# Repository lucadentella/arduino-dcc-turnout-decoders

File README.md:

# DCC turnout decoders and boards for Arduino

## :mega: Introduction / *Introduzione*
This repository contains all the resources for my tutorials about how to build DCC turnout (accessory) decoders with Arduino.

*Questo repository contiene tutte le risorse per i miei tutorial sulla costruzione di decoder scambi (accessori) DCC con Arduino.*

## :link: Links

 - [Youtube, Tutorial #1](https://youtu.be/FdMyOsOrDqg)
 - [Youtube, Tutorial #2](https://youtu.be/kijxEFWHnvc)
 - [Youtube, Tutorial #3](https://youtu.be/DjH3sCA5Gzo)
 - [Youtube, ServoShield](https://youtu.be/rDGcTmMk3Rc)
 - [Youtube, SoundShield](https://youtu.be/pyPB2XuQQIc)
 - [Youtube, Playlist](https://youtube.com/playlist?list=PL45uNmSXju7mn3bMtVVPlFQmpD3mUI5mi)
 
 - [Officina del Modellismo](https://www.officinamodellismo.com/), to buy our products / *per acquistare i nostri prodotti*
 - [Shared projects on PCBWay](https://www.pcbway.com/project/member/?bmbno=20B30179-F6D7-49), to order PCBs / *per ordinare i circuiti stampati*

## :barber: Boards / *Schede*
The [Eagle](https://github.com/lucadentella/arduino-dcc-turnout-decoders/tree/main/Eagle) subfolder contains [Eagle projects](https://www.autodesk.com/products/eagle/overview) to build the following boards (click on the board name to open the documentation with partlist, images...):

 - **[MosfetBoard](https://github.com/lucadentella/arduino-dcc-turnout-decoders/blob/main/Documentation/MosfetBoard.md)**, to control a solenoid motor using logic-level MOSFETs
 - **[PointMotorBoard](https://github.com/lucadentella/arduino-dcc-turnout-decoders/blob/main/Documentation/PointMotorBoard.md)**, to control two DC motors using an H-Bridge IC
 - **[CDU (Capacitor Discharge Unit)](https://github.com/lucadentella/arduino-dcc-turnout-decoders/blob/main/Documentation/CDU.md)**, to provide more current to actuators 
 - **[ServoShield](https://github.com/lucadentella/arduino-dcc-turnout-decoders/blob/main/Documentation/ServoShield.md)**, to create a Servo accessory decoder
 - **[SoundShield](https://github.com/lucadentella/arduino-dcc-turnout-decoders/blob/main/Documentation/SoundShield.md)**, to create a Sound accessory decoder

*La sottocartella [Eagle](https://github.com/lucadentella/arduino-dcc-turnout-decoders/tree/main/Eagle) contiene contiene dei [progetti Eagle](https://www.autodesk.com/products/eagle/overview) per realizzare le seguenti schede (clicca sul nome della scheda per aprire la relativa documentazione con elenco componenti, immagini...):*

 - **[MosfetBoard](https://github.com/lucadentella/arduino-dcc-turnout-decoders/blob/main/Documentation/MosfetBoard.md)**, per controllare un attuatore a solenoide usando logic-level MOSFETs
 - **[PointMotorBoard](https://github.com/lucadentella/arduino-dcc-turnout-decoders/blob/main/Documentation/PointMotorBoard.md)**, per controllare due motori in corrente continua usando un integrato H-Bridge
 - **[CDU (Capacitor Discharge Unit)](https://github.com/lucadentella/arduino-dcc-turnout-decoders/blob/main/Documentation/CDU.md)**, per fornire più corrente agli attuatori
 - **[ServoShield](https://github.com/lucadentella/arduino-dcc-turnout-decoders/blob/main/Documentation/ServoShield.md)**, per realizzare un decoder accessori per servocomandi
 - **[SoundShield](https://github.com/lucadentella/arduino-dcc-turnout-decoders/blob/main/Documentation/SoundShield.md)**, per realizzare un decoder accessori sonoro
 
## :clipboard: Sketches
The [Arduino](https://github.com/lucadentella/arduino-dcc-turnout-decoders/tree/main/Arduino) subfolder contains the sketches for implementing the decoders shown in the video tutorials.

*La sottocartella [Arduino](https://github.com/lucadentella/arduino-dcc-turnout-decoders/tree/main/Arduino) contiene i programmi (sketch) per realizzare i decoder mostrati nei video tutorials.*
 
## :factory: Documentation
The [Documentation](https://github.com/lucadentella/arduino-dcc-turnout-decoders/tree/main/Documentation) subfolder contains partlist, schematics

*La sottocartella [Documentation](https://github.com/lucadentella/arduino-dcc-turnout-decoders/tree/main/Documentation) contiene la lista dei componenti e gli schemi elettrici*

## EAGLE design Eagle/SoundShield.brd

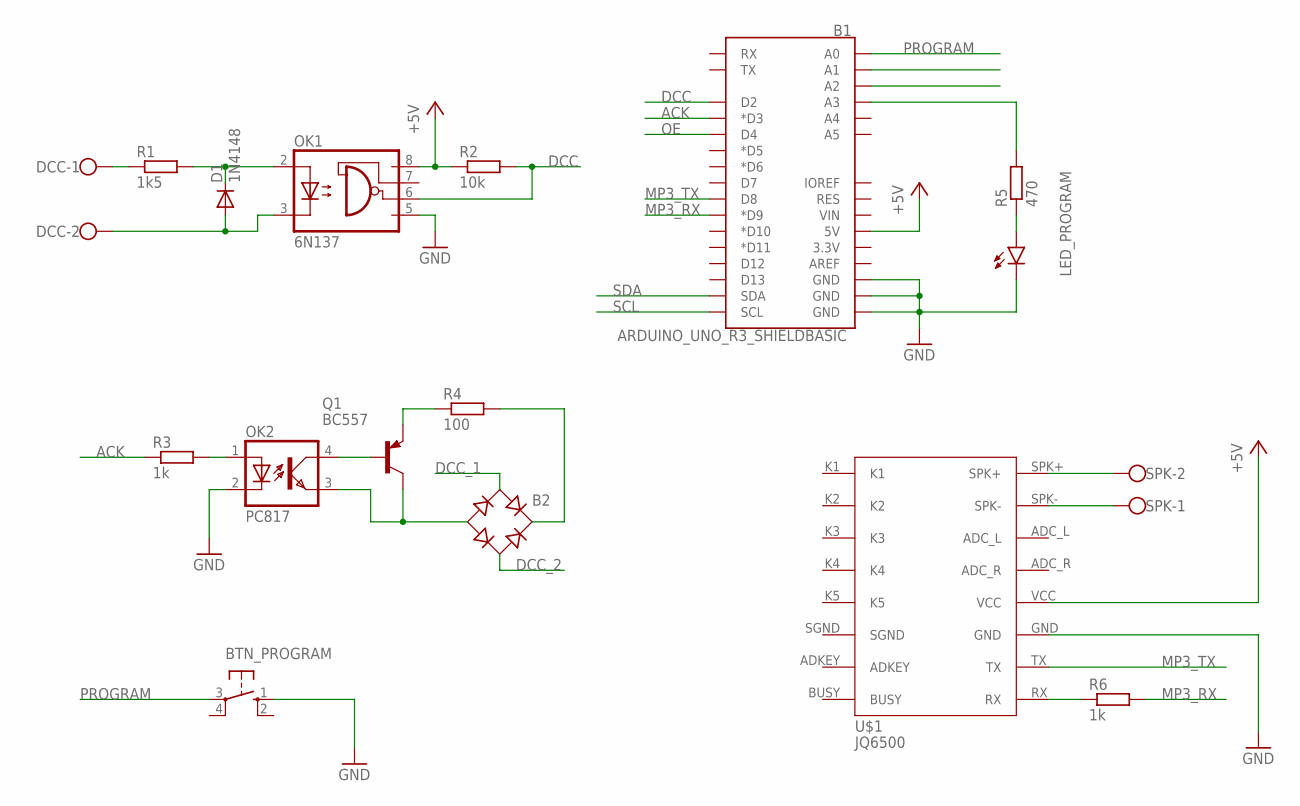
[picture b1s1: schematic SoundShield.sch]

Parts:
B1: ARDUINO_UNO_R3_SHIELDBASIC; UNO_R3_SHIELD
B2: RB1A
BTN_PROGRAM: 10-XX; B3F-10XX
D1: 1N4148; DO35-7
DCC: W237-102
LED_PROGRAM: LED3MM
OK1: 6N137; DIL08
OK2: PC817; DIL04
Q1: BC557; TO92
R1: 1k5; 0207/2V
R2: 10k; 0207/2V
R3, R6: 1k; 0207/2V
R4: 100; 0207/2V
R5: 470; 0207/2V
SPK: W237-102
U$1: JQ6500; JQ6500-PACKAGE

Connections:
+5V: B1.5V, OK1.8 (VCC), R2.1, U$1.VCC
ACK: B1.D3 (*D3), R3.1
DCC: B1.D2, OK1.6 (VO), R2.2
DCC_1: B2.AC1, DCC.1, R1.1
DCC_2: B2.AC2, D1.A, DCC.2, OK1.3 (C)
DOWN: B1.A2
GND: B1.GND@0 (GND), B1.GND@1 (GND), B1.GND@2 (GND), BTN_PROGRAM.1 (S), LED_PROGRAM.K (C), OK1.5 (GND), OK2.2 (C), U$1.GND
MP3_RX: B1.D9 (*D9), R6.2
MP3_TX: B1.D8, U$1.TX
unnamed: B2.-, OK2.3 (EMIT), Q1.3 (C)
unnamed: D1.C, OK1.2 (A), R1.2
unnamed: B1.A3, R5.2
unnamed: LED_PROGRAM.A, R5.1
unnamed: SPK.2, U$1.SPK+
unnamed: SPK.1, U$1.SPK-
unnamed: OK2.1 (A), R3.2
unnamed: OK2.4 (COL), Q1.2 (B)
unnamed: Q1.1 (E), R4.1
unnamed: B2.+, R4.2
unnamed: R6.1, U$1.RX
OE: B1.D4
PROGRAM: B1.A0, BTN_PROGRAM.3
SCL: B1.SCL
SDA: B1.SDA
UP: B1.A1

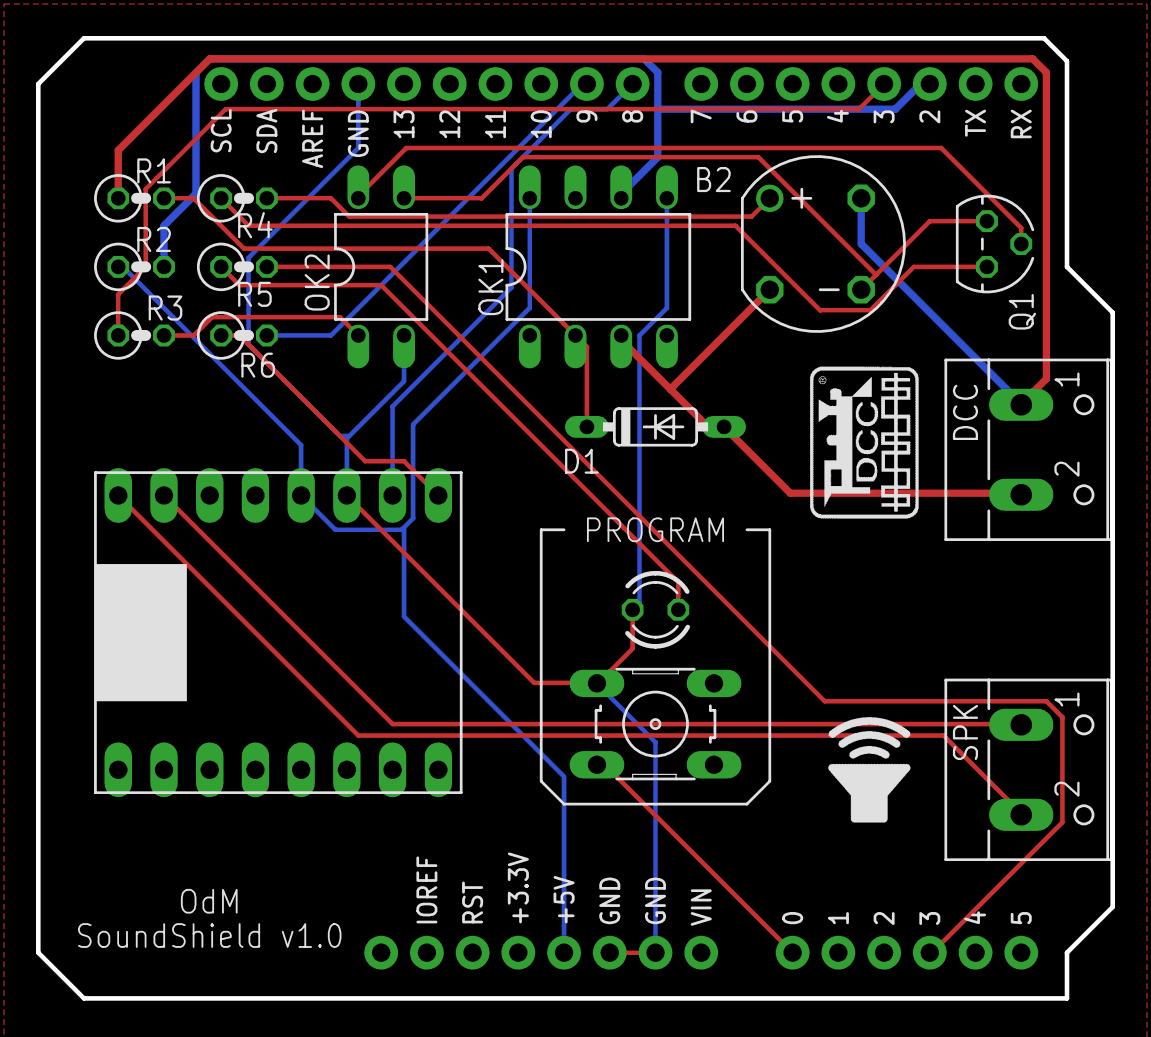
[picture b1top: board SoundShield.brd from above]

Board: 2 copper layers, 59.7 x 53.3 mm, 19 parts (0 on the bottom side), 20 nets.

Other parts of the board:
U$2: DCC_ICON
U$3: SPEAKER_ICON

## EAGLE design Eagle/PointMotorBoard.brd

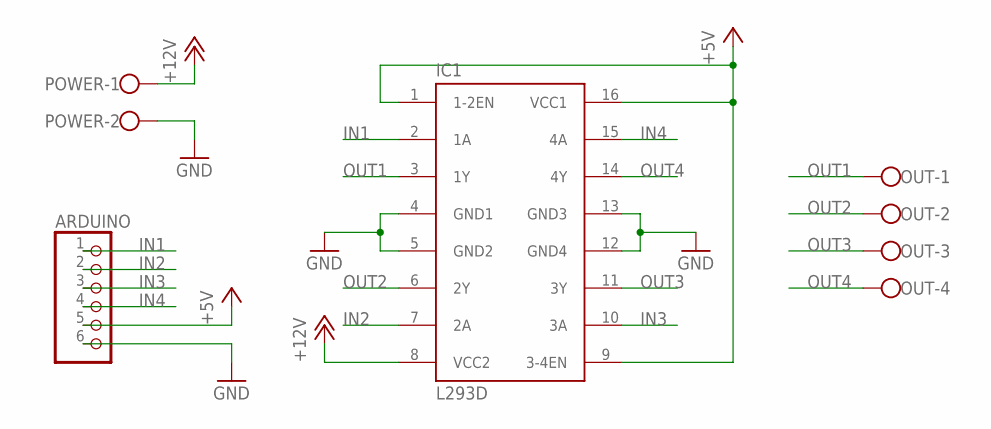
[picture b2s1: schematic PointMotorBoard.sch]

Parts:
ARDUINO: PINHD-1X6; 1X06
IC1: L293D; DIL16
OUT: W237-4
POWER: W237-102

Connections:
+5V: ARDUINO.5, IC1.1 (1-2EN), IC1.9 (3-4EN), IC1.16 (VCC1)
+12V: IC1.8 (VCC2), POWER.1
GND: ARDUINO.6, IC1.4 (GND1), IC1.5 (GND2), IC1.12 (GND4), IC1.13 (GND3), POWER.2
IN1: ARDUINO.1, IC1.2 (1A)
IN2: ARDUINO.2, IC1.7 (2A)
IN3: ARDUINO.3, IC1.10 (3A)
IN4: ARDUINO.4, IC1.15 (4A)
OUT1: IC1.3 (1Y), OUT.1
OUT2: IC1.6 (2Y), OUT.2
OUT3: IC1.11 (3Y), OUT.3
OUT4: IC1.14 (4Y), OUT.4

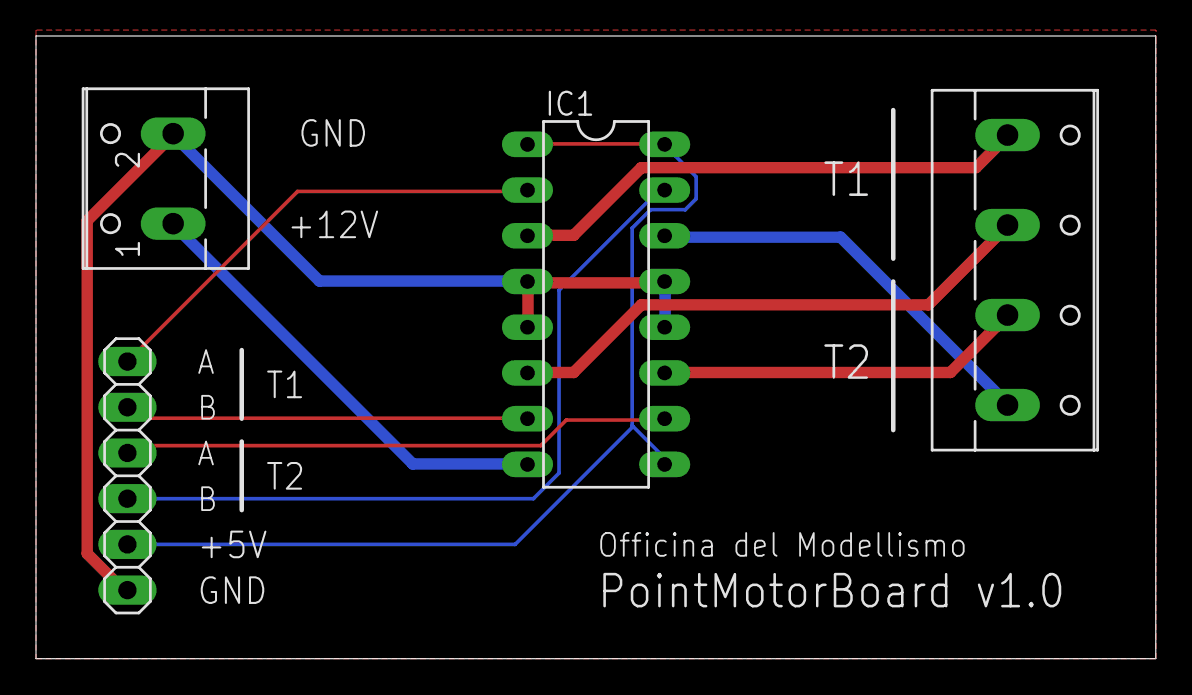
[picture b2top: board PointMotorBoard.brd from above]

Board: 2 copper layers, 62.2 x 34.6 mm, 4 parts (0 on the bottom side), 11 nets.

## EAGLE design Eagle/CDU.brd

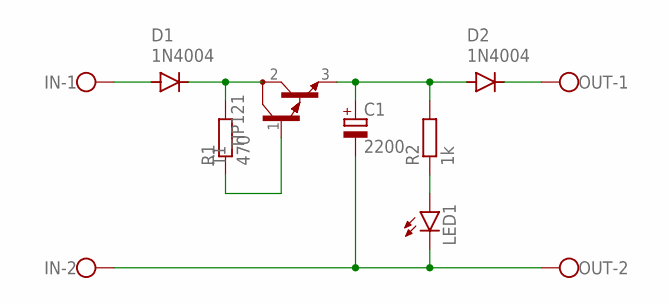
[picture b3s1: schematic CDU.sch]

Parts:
C1: 2200; E7,5-18
D1, D2: 1N4004; DO41-10
IN: W237-102
LED1: LED5MM
OUT: W237-102
R1: 470; 0411/15
R2: 1k; 0207/10
T1: TIP121; TO220V

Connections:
unnamed: D1.A, IN.1
unnamed: D1.C, R1.2, T1.2 (C)
unnamed: R1.1, T1.1 (B)
unnamed: C1.+, D2.A, R2.2, T1.3 (E)
unnamed: D2.C, OUT.1
unnamed: LED1.A, R2.1
unnamed: C1.-, IN.2, LED1.K (C), OUT.2

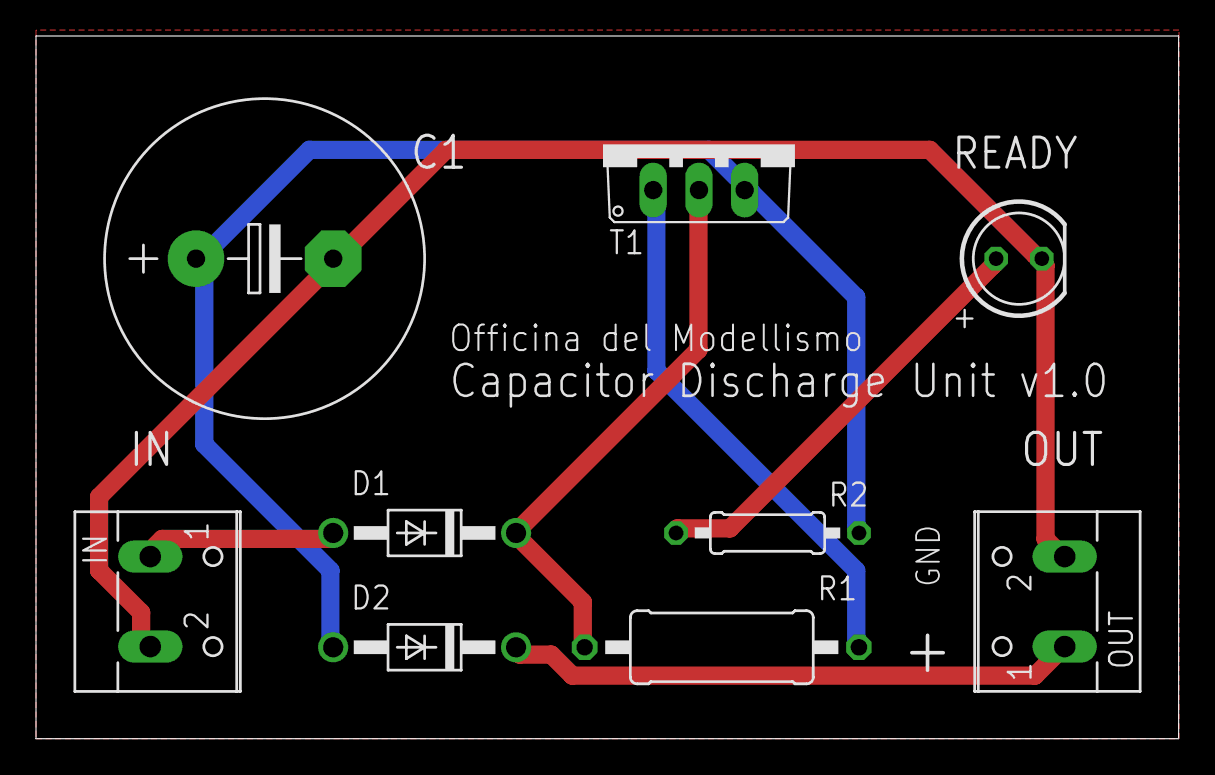
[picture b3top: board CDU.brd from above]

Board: 2 copper layers, 63.5 x 39.0 mm, 9 parts (0 on the bottom side), 7 nets.

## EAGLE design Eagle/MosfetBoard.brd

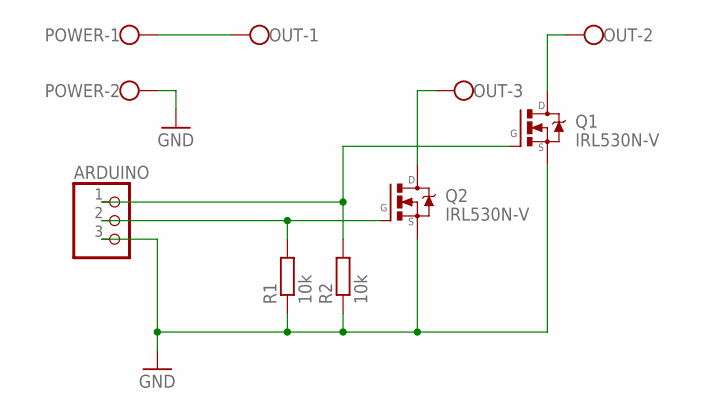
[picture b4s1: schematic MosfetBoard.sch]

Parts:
ARDUINO: PINHD-1X3; 1X03
OUT: W237-103
POWER: W237-102
Q1, Q2: IRL530N-V; TO220V
R1, R2: 10k; 0207/10

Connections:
GND: ARDUINO.3, POWER.2, Q1.3 (S), Q2.3 (S), R1.1, R2.1
unnamed: OUT.1, POWER.1
unnamed: ARDUINO.2, Q2.1 (G), R1.2
unnamed: OUT.3, Q2.2 (D)
unnamed: OUT.2, Q1.2 (D)
POS_A: ARDUINO.1, Q1.1 (G), R2.2

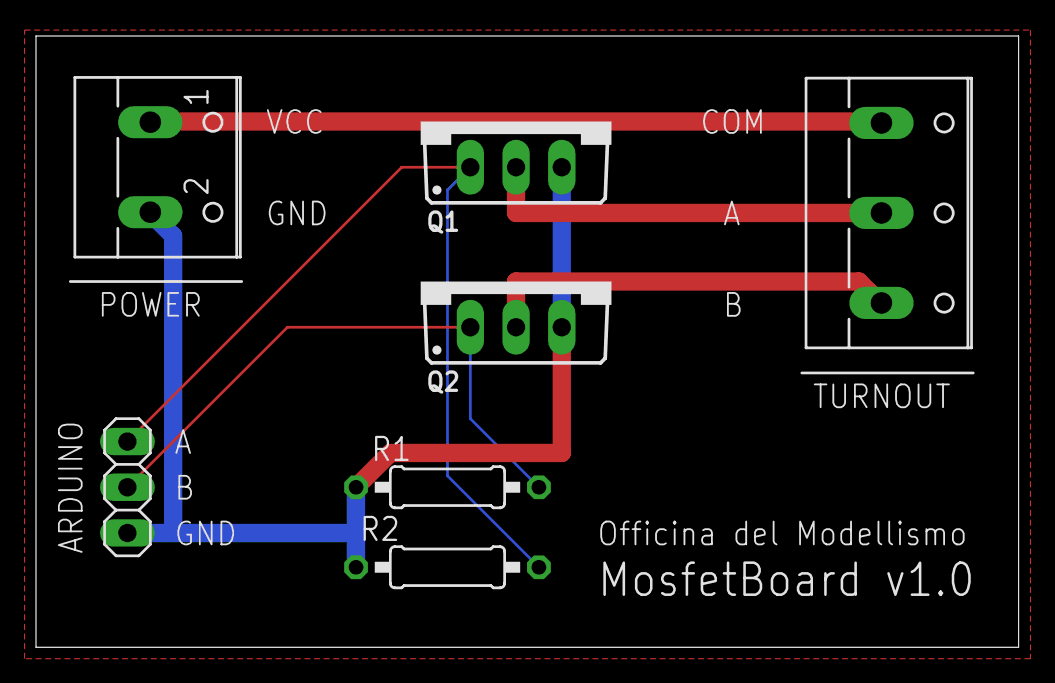
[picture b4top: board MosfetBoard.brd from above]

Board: 2 copper layers, 54.6 x 34.0 mm, 7 parts (0 on the bottom side), 6 nets.

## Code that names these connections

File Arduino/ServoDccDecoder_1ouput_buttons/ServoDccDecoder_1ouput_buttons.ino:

// DCC Decoder for servo, 1 output + buttons to program CVs
// Luca Dentella
//
// Playlist of my tutorials: https://youtube.com/playlist?list=PL45uNmSXju7mn3bMtVVPlFQmpD3mUI5mi

#include <NmraDcc.h>
#include <Servo.h>

// PIN definitions
#define DCC_PIN       2
#define ACK_PIN       3
#define SERVO_PIN     8
#define RESET_PIN     4
#define LED_PIN       13
#define PROGRAM_PIN   A0
#define UP_PIN        A1
#define DOWN_PIN      A2

// Custom CVs
// Position value is 1000 + (CV_VALUE * 4)uS, for example for position = 2000uS set CV=250
// Speed is a multiple of 100milliseconds, for example for 2 seconds set CV=20
#define CV_A_POSITION     30
#define CV_B_POSITION     31
#define CV_SPEED          32
#define CV_LAST_POSITION  33

// Default values for CVs
#define DECODER_ADDR          4
#define DEFAULT_A_POSITION    20
#define DEFAULT_B_POSITION    200
#define DEFAULT_SPEED         30
#define DEFAULT_LAST_POSITION 0

// Global variables
NmraDcc Dcc;
Servo myServo;
byte aPosition, bPosition, speed;
byte currentPosition, targetPosition;
int steps;
int stepDelay;
long lastStepTime = 0;
bool servoMoving = false;
bool servoSweep = false;
bool AtoBdirection = false;
bool directionForward = true;
char serialBuffer[100];
bool programmingMode = false;
bool isProgramButtonDown = false;
long lastProgramButtonDown = 0;

// Move servo to the target position with the configured speed
void moveServoToTargetPosition(byte position) {
  
  // get the number of steps to move from currentPosition to targetPosition
  targetPosition = position;

  if(targetPosition > currentPosition) {
    directionForward = true;
    steps = targetPosition - currentPosition;
  } else {
    directionForward = false;
    steps = currentPosition - targetPosition;    
  }

  if(steps > 0) {

    // get the delay between each step to match the speed, in milliseconds
    stepDelay = (speed * 100) / steps;

    // start the movement (controlled in the main loop())
    lastStepTime = millis();
    servoMoving = true;

    char buf[100];
    sprintf(buf, "Moving servo from position %d to position %d with %d steps every %dms", currentPosition, targetPosition, steps, stepDelay);
    Serial.println(buf);
  }
}

// DCC acccessory decoder command received
void notifyDccAccTurnoutOutput(uint16_t Addr, uint8_t Direction, uint8_t OutputPower) {

  Serial.print("Got ");
  Serial.println(Addr);

  // If servo is already moving or programming mode is active, ignore the command
  if (servoMoving || programmingMode) return;

  // Command sent to our address?
  if(Addr == Dcc.getAddr()) {

    if(Direction == 0) moveServoToTargetPosition(aPosition);
    else moveServoToTargetPosition(bPosition);
  }
}

void notifyCVAck(void) {

  digitalWrite(ACK_PIN, HIGH);
  delay(8);  
  digitalWrite(ACK_PIN, LOW);
}

// Factory reset (write to CV8)
void notifyCVResetFactoryDefault() {

  // Reset CVs to the default value
  Dcc.setCV(CV_ACCESSORY_DECODER_ADDRESS_LSB, DECODER_ADDR & 0xFF);
  Dcc.setCV(CV_ACCESSORY_DECODER_ADDRESS_MSB, DECODER_ADDR >> 8);
  Dcc.setCV(CV_A_POSITION, DEFAULT_A_POSITION);
  Dcc.setCV(CV_B_POSITION, DEFAULT_B_POSITION);
  Dcc.setCV(CV_SPEED, DEFAULT_SPEED);
  Dcc.setCV(CV_LAST_POSITION, DEFAULT_LAST_POSITION);

  // Reset global variables
  aPosition = DEFAULT_A_POSITION;
  bPosition = DEFAULT_B_POSITION;
  speed = DEFAULT_SPEED;

  Serial.println("Factory reset:");
  sprintf(serialBuffer, "Address = %d, A Position = %d, B Position = %d, Speed = %d", DECODER_ADDR, DEFAULT_A_POSITION, DEFAULT_B_POSITION, DEFAULT_SPEED);
  Serial.println(serialBuffer);
  Serial.println();
};

void setup() {

  Serial.begin(115200);
  Serial.println("Servo Decoder");
  Serial.println();

  // Set pins direction
  pinMode(RESET_PIN, INPUT_PULLUP);
  pinMode(PROGRAM_PIN, INPUT_PULLUP);
  pinMode(UP_PIN, INPUT_PULLUP);
  pinMode(DOWN_PIN, INPUT_PULLUP);
  pinMode(LED_PIN, INPUT_PULLUP);
  
  // Initialize servo library
  myServo.attach(SERVO_PIN);

  // Initialize DCC library
  Dcc.pin(digitalPinToInterrupt(DCC_PIN), DCC_PIN, false);
  Dcc.init(MAN_ID_DIY, 1, FLAGS_DCC_ACCESSORY_DECODER | FLAGS_OUTPUT_ADDRESS_MODE, 0);

  // Check if reset pin is LOW -> perform a factory reset
  if(digitalRead(RESET_PIN) == LOW) notifyCVResetFactoryDefault();

  // Read CVs into global variables
  aPosition = Dcc.getCV(CV_A_POSITION);
  bPosition = Dcc.getCV(CV_B_POSITION);
  speed = Dcc.getCV(CV_SPEED);
  Serial.println("Values read from CVs:");
  sprintf(serialBuffer, "Address = %d, A Position = %d, B Position = %d, Speed = %d", Dcc.getAddr(), aPosition, bPosition, speed);
  Serial.println(serialBuffer);
  Serial.println();  

  // Move the servo immediately to the last position
  if(Dcc.getCV(CV_LAST_POSITION) == 0) currentPosition = aPosition;
  else currentPosition = bPosition;
  myServo.writeMicroseconds(currentPosition * 4 + 1000);
  sprintf(serialBuffer, "Servo moved to the last saved position, %d", currentPosition);
  Serial.println(serialBuffer);
  Serial.println("Decoder ready!");
}

void loop() {

  // Process incoming DCC packets
  Dcc.process();

  // Check / execute programming mode
  checkProgrammingMode();

  // Check if servo is moving
  if(servoMoving) {

    long currentTime = millis();

    // If the stepDelay has passed, do a step
    if(currentTime - lastStepTime > stepDelay) {

      if(directionForward) currentPosition = currentPosition + 1;
      else currentPosition = currentPosition - 1;
      myServo.writeMicroseconds(currentPosition * 4 + 1000);
      lastStepTime = currentTime;

      // If servo has reached the target position, stop
      if(currentPosition == targetPosition) {
        servoMoving = false;
        Serial.println("Target position reached");
        Dcc.setCV(CV_LAST_POSITION, targetPosition);
      }
    }
  }

  // Check if sweep mode is active
  if(servoSweep) {

    long currentTime = millis();

    // If the stepDelay has passed, do a step
    if(currentTime - lastStepTime > stepDelay) {

      if(directionForward) currentPosition = currentPosition + 1;
      else currentPosition = currentPosition - 1;
      myServo.writeMicroseconds(currentPosition * 4 + 1000);
      lastStepTime = currentTime;

      // If servo has reached the target position, revert direction
      if(currentPosition == targetPosition) {
        
        if(AtoBdirection) {
          if(bPosition < aPosition) {
            directionForward = true;
            steps = aPosition - bPosition;
          } else {
            directionForward = false;
            steps = bPosition - aPosition;            
          }          
          AtoBdirection = false;
          targetPosition = aPosition;
        } else {
          if(aPosition < bPosition) {
            directionForward = true;
            steps = bPosition - aPosition;
          } else {
            directionForward = false;
            steps = aPosition - bPosition;            
          }
          AtoBdirection = true;
          targetPosition = bPosition;
        }
      }
      stepDelay = (speed * 100) / steps;
    }
  }  
}

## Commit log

2022-11-12 Sketches for solenoid decoders added
2022-11-12 Some updates
2022-11-12 Typos fixed
2022-11-12 Documentation for MosfetBoard added
2022-11-12 Dynamic address
2023-04-02 CDU and DC motor added
2023-04-14 New tutorial added
2023-05-14 Servo decoders added
2023-05-14 Link to tutorial #3 added
2023-05-14 Link fixed
2023-09-18 ServoShield sketch added
2023-09-18 ServoShield documentation added
2023-09-25 ServoShield documentation updated
2023-10-30 SoundShield added
2023-11-01 New updates
2023-11-01 Fix typo

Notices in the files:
parts and their libraries:
SparkFun-Boards: Licensing: Creative Commons ShareAlike 4.0 International - https://creativecommons.org/licenses/by-sa/4.0
